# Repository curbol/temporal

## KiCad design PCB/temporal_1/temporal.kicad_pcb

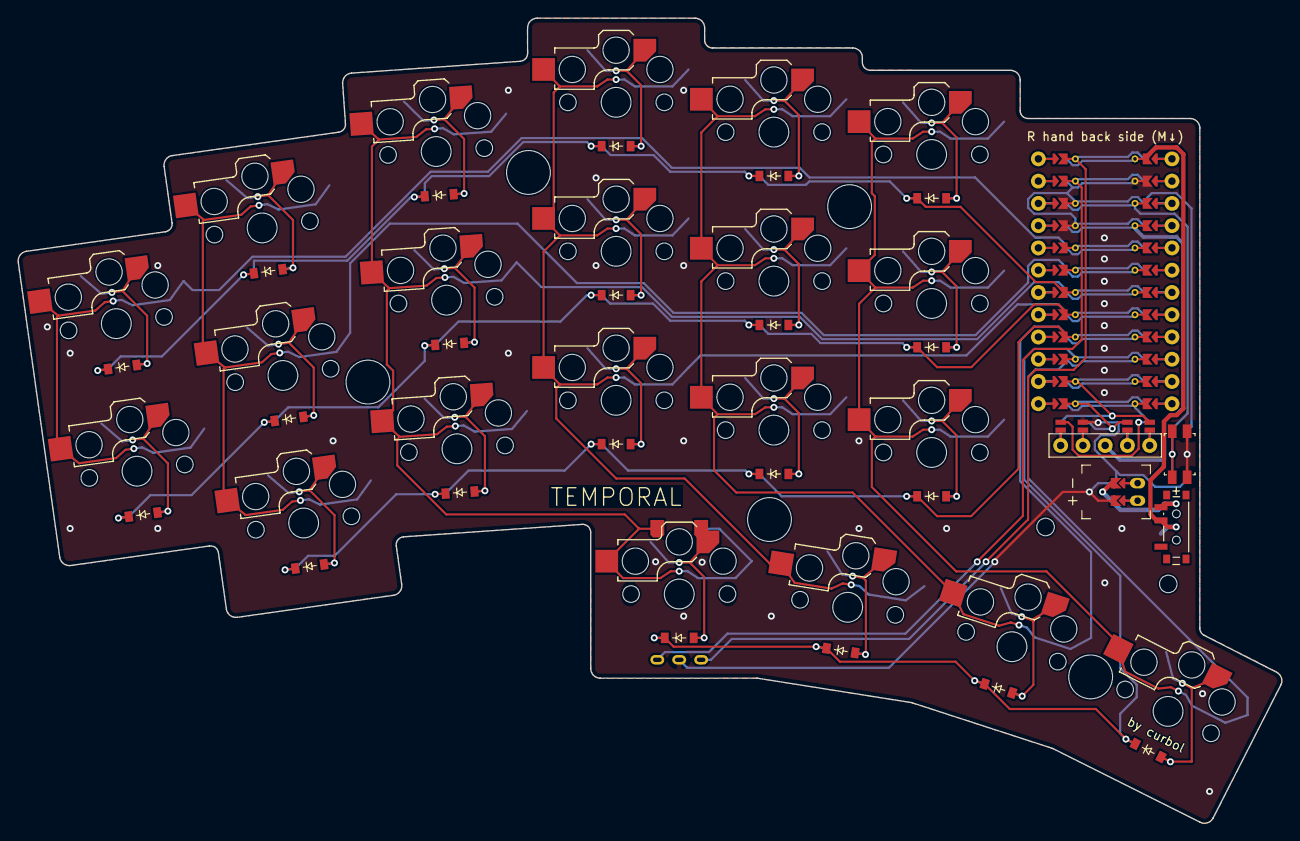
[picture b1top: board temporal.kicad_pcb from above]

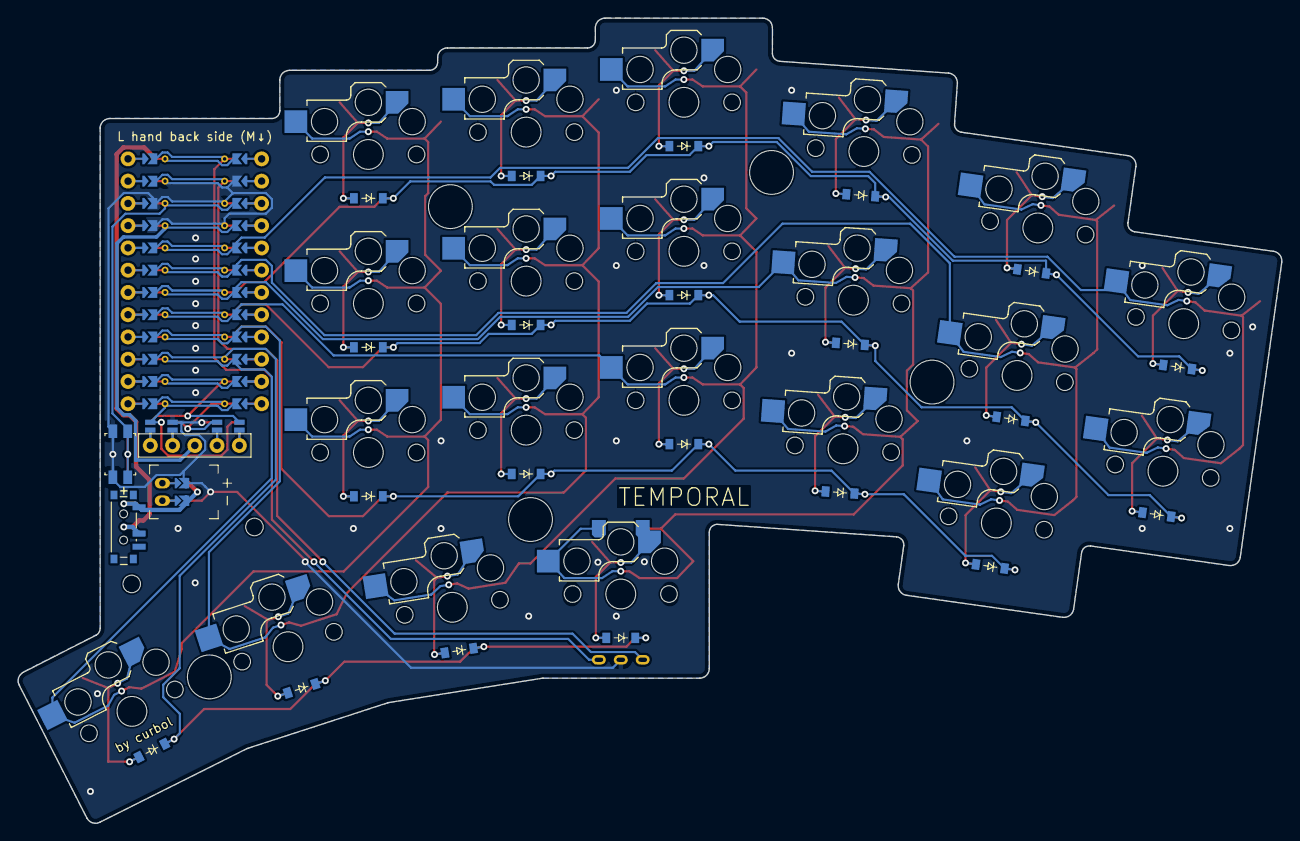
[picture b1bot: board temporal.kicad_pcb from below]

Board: 2 copper layers, 144.2 x 91.9 mm, 55 parts (21 on the bottom side), 47 nets.

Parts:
D1, D2, D3, D4, D5, D6, D7, D8, D9, D10, D11, D12, D13, D14, D15, D16, D17, D18, D19, D20, D21: diode_tht_sod123
DISP1: display_nice_view
JST1: battery_connector_jst_ph_2
MCU1: mcu_nice_nano
MH1, MH2, MH3, MH4, MH5, MH6, MH7: mounting_hole_npth
PWR1: power_switch_smd_side
RE1: rotary_encoder_ec11_ec12
RST1: reset_switch_smd_side
S1, S2, S3, S4, S5, S6, S7, S8, S9, S10, S11, S12, S13, S14, S15, S16, S17, S18, S19, S20, S21: switch_choc_v1_v2

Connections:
BAT_P: JST1.1, PWR1.1, PWR1.3
CS: DISP1.14, DISP1.24, MCU1.112
DISP1_1: DISP1.1, DISP1.10, DISP1.23
DISP1_2: DISP1.2, DISP1.11, DISP1.22
DISP1_4: DISP1.4, DISP1.12, DISP1.21
DISP1_5: DISP1.5, DISP1.13, DISP1.20
GND: DISP1.15, DISP1.25, JST1.2, MCU1.102, MCU1.121, MCU1.122, RE1.C, RST1.1, RST1.3
JST1_1: JST1.11, JST1.21, JST1.31
JST1_2: JST1.12, JST1.22, JST1.32
MOSI: DISP1.17, DISP1.27, MCU1.114
RAW: MCU1.101, PWR1.2
RST: MCU1.103, RST1.2, RST1.4
SCK: DISP1.16, DISP1.26, MCU1.113
VCC: DISP1.3, MCU1.104
col_extra: MCU1.105, S1.2, S2.2
col_index: MCU1.109, S12.2, S13.2, S14.2, S20.2
col_inner: MCU1.110, S15.2, S16.2, S17.2, S21.2
col_middle: MCU1.108, S9.2, S10.2, S11.2, S19.2
col_pinky: MCU1.106, S3.2, S4.2, S5.2
col_ring: MCU1.107, RE1.S1, S6.2, S7.2, S8.2, S18.2
encoder_a: MCU1.123, RE1.A
encoder_b: MCU1.124, RE1.B
encoder_thumb: D18.2, RE1.S2, S18.1
extra_home: D1.2, S1.1
extra_top: D2.2, S2.1
far_thumb: D21.2, S21.1
index_bottom: D12.2, S12.1
index_home: D13.2, S13.1
index_top: D14.2, S14.1
inner_bottom: D15.2, S15.1
inner_home: D16.2, S16.1
inner_top: D17.2, S17.1
mid_thumb: D20.2, S20.1
middle_bottom: D9.2, S9.1
middle_home: D10.2, S10.1
middle_top: D11.2, S11.1
near_thumb: D19.2, S19.1
pinky_bottom: D3.2, S3.1
pinky_home: D4.2, S4.1
pinky_top: D5.2, S5.1
ring_bottom: D6.2, S6.1
ring_home: D7.2, S7.1
ring_top: D8.2, S8.1
row_bottom: D3.1, D6.1, D9.1, D12.1, D15.1, MCU1.116
row_home: D1.1, D4.1, D7.1, D10.1, D13.1, D16.1, MCU1.117
row_thumb: D18.1, D19.1, D20.1, D21.1, MCU1.115
row_top: D2.1, D5.1, D8.1, D11.1, D14.1, D17.1, MCU1.118
